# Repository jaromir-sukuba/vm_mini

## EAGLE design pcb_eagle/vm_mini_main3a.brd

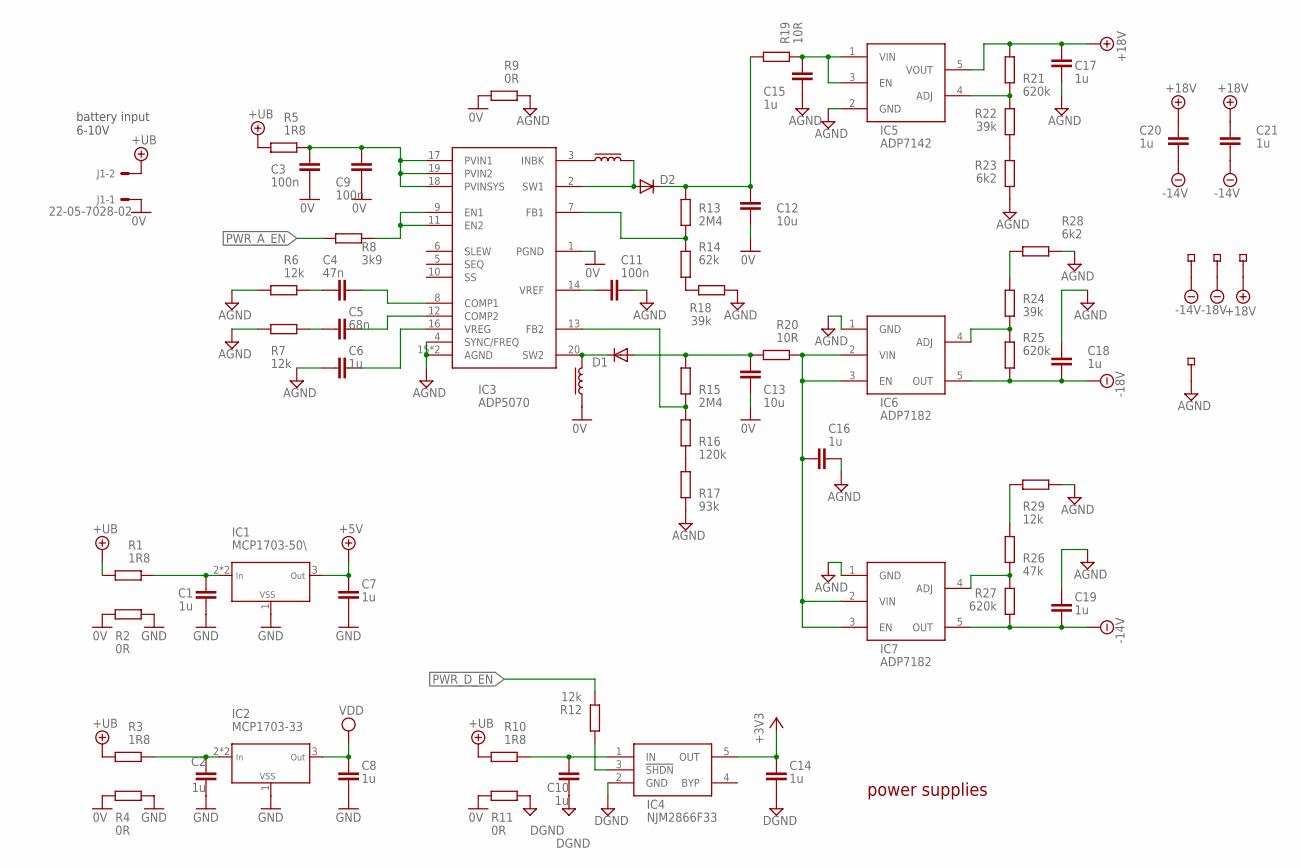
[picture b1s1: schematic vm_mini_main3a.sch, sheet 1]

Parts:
C1, C2, C6, C7, C8, C10, C14, C15, C16, C17, C18, C19, C20, C21: 1u; R0805
C3, C9, C11: 100n; R0805
C4: 47n; R0805
C5: 68n; R0805
C12, C13: 10u; R0805
D1, D2: DIODE-MINIMELF; MINIMELF
IC1: MCP1703-50\; SOT89
IC2: MCP1703-33; SOT89
IC3: ADP5070; TSSOP20-EP
IC4: NJM2866F33; SOT23-5
IC5: ADP7142; SOT23-5L
IC6, IC7: ADP7182; SOT23-5L
J1: 22-05-7028-02; 7395-02
L1, L2: INDUCTORBOURNS_SRP7030; BOURNS_SRP7030
R1, R3, R5, R10: 1R8; R_MINIMELF
R2, R4, R9, R11: 0R; R_MINIMELF
R6, R7, R12, R29: 12k; R_MINIMELF
R8: 3k9; R_MINIMELF
R13, R15: 2M4; R_MINIMELF
R14: 62k; R_MINIMELF
R16: 120k; R_MINIMELF
R17: 93k; R_MINIMELF
R18, R22, R24: 39k; R_MINIMELF
R19, R20: 10R; R_MINIMELF
R21, R25, R27: 620k; R_MINIMELF
R23, R28: 6k2; R_MINIMELF
R26: 47k; R_MINIMELF
TP1, TP2, TP3, TP4: TEST_PADSMD_35X2; TP_SMD_35X2

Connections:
0V: C3.2, C9.2, C12.2, C13.1, IC3.1 (PGND), J1.1, L1.P$1, R2.P$2 (2), R4.P$2 (2), R9.P$2 (2), R11.P$2 (2)
+3V3: C14.2, IC4.5 (OUT); also elsewhere on the board
+5V: C7.2, IC1.3 (OUT); also elsewhere on the board
+18V: C17.1, C20.1, C21.1, IC5.5 (VOUT), R21.P$2 (2), TP3.P$1; also elsewhere on the board
+UB: J1.2, R1.P$2 (2), R3.P$2 (2), R5.P$2 (2), R10.P$2 (2); also elsewhere on the board
-14V: C19.2, C20.2, C21.2, IC7.5 (OUT), R27.P$2 (2), TP1.P$1; also elsewhere on the board
-18V: C18.2, IC6.5 (OUT), R25.P$2 (2), TP2.P$1; also elsewhere on the board
AGND: C6.1, C11.1, C15.2, C16.2, C17.2, C18.1, C19.1, IC3.4 (SYNC/FREQ), IC3.15 (AGND), IC3.EP (AGND), IC5.2 (GND), IC6.1 (GND), IC7.1 (GND), R6.P$2 (2), R7.P$2 (2), R9.P$1 (1), R17.P$1 (1), R18.P$2 (2), R23.P$2 (2), R28.P$2 (2), R29.P$2 (2), TP4.P$1; also elsewhere on the board
DGND: C10.1, C14.1, IC4.2 (GND), R11.P$1 (1); also elsewhere on the board
GND: C1.1, C2.1, C7.1, C8.1, IC1.1 (VSS), IC2.1 (VSS), R2.P$1 (1), R4.P$1 (1); also elsewhere on the board
unnamed: IC3.9 (EN1), IC3.11 (EN2), R8.P$1 (1)
unnamed: IC4.3 (!SHDN), R12.P$2 (2)
unnamed: R24.P$2 (2), R28.P$1 (1)
unnamed: C16.1, IC6.2 (VIN), IC6.3 (EN), IC7.2 (VIN), IC7.3 (EN), R20.P$1 (1)
unnamed: C15.1, IC5.1 (VIN), IC5.3 (EN), R19.P$1 (1)
unnamed: IC3.3 (INBK), L2.P$1
unnamed: D1.C, IC3.20 (SW2), L1.P$2
unnamed: D2.A, IC3.2 (SW1), L2.P$2
unnamed: C3.1, C9.1, IC3.17 (PVIN1), IC3.18 (PVINSYS), IC3.19 (PVIN2), R5.P$1 (1)
unnamed: IC5.4 (ADJ), R21.P$1 (1), R22.P$1 (1)
unnamed: C11.2, IC3.14 (VREF)
unnamed: C12.1, D2.C, R13.P$1 (1), R19.P$2 (2)
unnamed: C4.1, R6.P$1 (1)
unnamed: IC3.13 (FB2), R15.P$1 (1), R16.P$2 (2)
unnamed: C5.1, R7.P$1 (1)
unnamed: IC3.7 (FB1), R13.P$2 (2), R14.P$1 (1)
unnamed: IC6.4 (ADJ), R24.P$1 (1), R25.P$1 (1)
unnamed: C4.2, IC3.8 (COMP1)
unnamed: C5.2, IC3.12 (COMP2)
unnamed: C6.2, IC3.16 (VREG)
unnamed: C13.2, D1.A, R15.P$2 (2), R20.P$2 (2)
unnamed: C10.2, IC4.1 (IN), R10.P$1 (1)
unnamed: C2.2, IC2.2 (IN), IC2.2@1 (IN), R3.P$1 (1)
unnamed: C1.2, IC1.2 (IN), IC1.2@1 (IN), R1.P$1 (1)
unnamed: IC7.4 (ADJ), R26.P$1 (1), R27.P$1 (1)
unnamed: R22.P$2 (2), R23.P$1 (1)
unnamed: R26.P$2 (2), R29.P$1 (1)
unnamed: R16.P$1 (1), R17.P$2 (2)
unnamed: R14.P$2 (2), R18.P$1 (1)
PWR_A_EN: R8.P$2 (2); also elsewhere on the board
PWR_D_EN: R12.P$1 (1); also elsewhere on the board
VDD: C8.2, IC2.3 (OUT); also elsewhere on the board

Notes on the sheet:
power supplies
battery input 6-10V

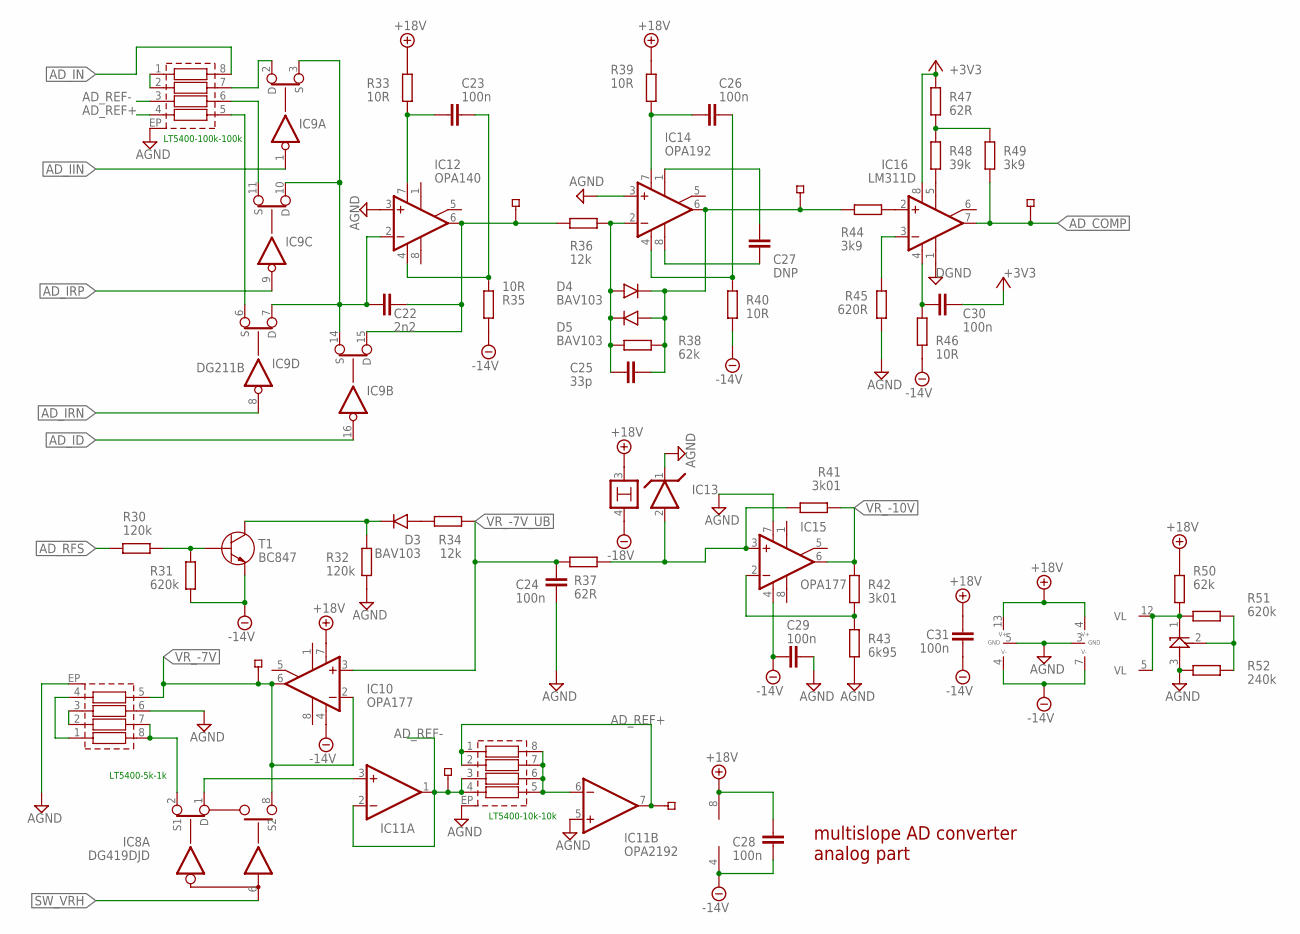
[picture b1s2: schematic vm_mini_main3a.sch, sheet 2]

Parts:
C22: 2n2; C150-054X183
C23, C26, C28, C29, C30, C31: 100n; R0805
C24: 100n; C050-035X075
C25: 33p; R_MINIMELF
C27: DNP; R_MINIMELF
D3, D4, D5: BAV103; SOD-80
IC8: DG419DJD; SO08
IC9: DG211B; SO16
IC10, IC15: OPA177; SO08
IC11: OPA2192; SO08
IC12: OPA140; SO08
IC13: LM399H; TO39/4
IC14: OPA192; SO08
IC16: LM311D; SO08
IC17: TL431_SOT23; SOT23
R30, R32: 120k; R_MINIMELF
R31, R51: 620k; R_MINIMELF
R33, R35, R39, R40, R46: 10R; R_MINIMELF
R34, R36: 12k; R_MINIMELF
R37, R47: 62R; R_MINIMELF
R38, R50: 62k; R_MINIMELF
R41, R42: 3k01; R_TR191
R43: 6k95; R_TR191
R44, R49: 3k9; R_MINIMELF
R45: 620R; R_MINIMELF
R48: 39k; R_MINIMELF
R52: 240k; R_MINIMELF
RN1: LT5400-5k-1k; MSOP8-EP
RN2: LT5400-100k-100k; MSOP8-EP
RN3: LT5400-10k+10k; MSOP8-EP
T1: BC847; SOT23
TP5, TP6, TP7, TP8, TP9, TP21: TEST_PADSMD_35X2; TP_SMD_35X2

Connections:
+3V3: C30.1, IC16.8 (V+), R47.P$2 (2); also elsewhere on the board
+18V: C28.2, C31.2, IC8.4 (V+), IC9.13 (V+), IC10.7 (V+), IC11.8 (V+), IC13.3, R33.P$2 (2), R39.P$2 (2), R50.P$1 (1); also elsewhere on the board
-14V: C28.1, C29.1, C31.1, IC8.7 (V-), IC9.4 (V-), IC10.4 (V-), IC11.4 (V-), IC15.4 (V-), R31.P$1 (1), R35.P$2 (2), R40.P$2 (2), R46.P$2 (2), T1.2 (E); also elsewhere on the board
-18V: IC13.4; also elsewhere on the board
AD_COMP: IC16.7 (OUT), R49.P$1 (1), TP7.P$1; also elsewhere on the board
AD_ID: IC9.16 (IN); also elsewhere on the board
AD_IIN: IC9.1 (IN); also elsewhere on the board
AD_IN: RN2.8 (R1B); also elsewhere on the board
AD_IRN: IC9.8 (IN); also elsewhere on the board
AD_IRP: IC9.9 (IN); also elsewhere on the board
AD_REF+: IC11.7 (OUT), RN2.4 (R4A), RN3.1 (R1A), RN3.2 (R2A), TP8.P$1
AD_REF-: IC11.1 (OUT), IC11.2 (-IN), RN2.3 (R3A), RN3.3 (R3A), RN3.4 (R4A), TP9.P$1
AD_RFS: R30.P$2 (2); also elsewhere on the board
AGND: C24.2, C29.2, IC8.3 (GND), IC9.5 (GND), IC11.5 (+IN), IC12.3 (+IN), IC13.1, IC14.3 (+IN), IC15.7 (V+), IC17.3 (A), R32.P$2 (2), R43.P$1 (1), R45.P$2 (2), R52.P$1 (1), RN1.6 (R3B), RN1.EP (SH), RN2.EP (SH), RN3.EP (SH); also elsewhere on the board
DGND: IC16.1 (GND); also elsewhere on the board
unnamed: C22.1, IC9.3 (S), IC9.7 (D), IC9.10 (D), IC9.14 (S), IC12.2 (-IN)
unnamed: IC15.2 (-IN), R42.P$2 (2), R43.P$2 (2)
unnamed: IC9.2 (D), RN2.7 (R2B)
unnamed: C22.2, IC9.15 (D), IC12.6 (OUT), R36.P$1 (1), TP5.P$1
unnamed: IC9.11 (S), RN2.6 (R3B)
unnamed: IC9.6 (S), RN2.5 (R4B)
unnamed: C23.2, IC12.7 (V+), R33.P$1 (1)
unnamed: C23.1, IC12.4 (V-), R35.P$1 (1)
unnamed: IC8.1 (D), IC11.3 (+IN)
unnamed: RN1.1 (R1A), RN1.4 (R4A)
unnamed: D3.A, R34.P$2 (2)
unnamed: IC8.2 (S1), RN1.7 (R2B), RN1.8 (R1B)
unnamed: IC13.2, IC15.3 (+IN), R37.P$1 (1), R41.P$2 (2)
unnamed: C25.P$1 (1), D4.A, D5.K, IC14.2 (-IN), R36.P$2 (2), R38.P$1 (1)
unnamed: R30.P$1 (1), R31.P$2 (2), T1.1 (B)
unnamed: D3.K, R32.P$1 (1), T1.3 (C)
unnamed: RN2.1 (R1A), RN2.2 (R2A)
unnamed: IC11.6 (-IN), RN3.5 (R4B), RN3.6 (R3B), RN3.7 (R2B), RN3.8 (R1B)
unnamed: RN1.2 (R2A), RN1.3 (R3A)
unnamed: C26.2, IC14.7 (V+), R39.P$1 (1)
unnamed: C26.1, IC14.4 (V-), R40.P$1 (1)
unnamed: C25.P$2 (2), D4.K, D5.A, IC14.6 (OUT), R38.P$2 (2), R44.P$1 (1), TP6.P$1
unnamed: IC16.5 (ON), R48.P$1 (1)
unnamed: R47.P$1 (1), R48.P$2 (2), R49.P$2 (2)
unnamed: C30.2, IC16.4 (V-), R46.P$1 (1)
unnamed: IC16.2 (+IN), R44.P$2 (2)
unnamed: IC16.3 (-IN), R45.P$1 (1)
unnamed: IC17.2 (R), R51.P$2 (2), R52.P$2 (2)
unnamed: IC8.5 (VL), IC9.12 (VL), IC17.1 (C), R50.P$2 (2), R51.P$1 (1)
unnamed: C27.P$1 (1), IC14.8 (OPT)
unnamed: C27.P$2 (2), IC14.1 (ON1)
SW_VRH: IC8.6 (IN)
VR_-7V: IC8.8 (S2), IC10.2 (-IN), IC10.6 (OUT), RN1.5 (R4B), TP21.P$1; also elsewhere on the board
VR_-7V_UB: C24.1, IC10.3 (+IN), R34.P$1 (1), R37.P$2 (2)
VR_-10V: IC15.6 (OUT), R41.P$1 (1), R42.P$1 (1)

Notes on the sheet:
LT5400-5k-1k
LT5400-10k-10k
LT5400-100k-100k
multislope AD converter analog part

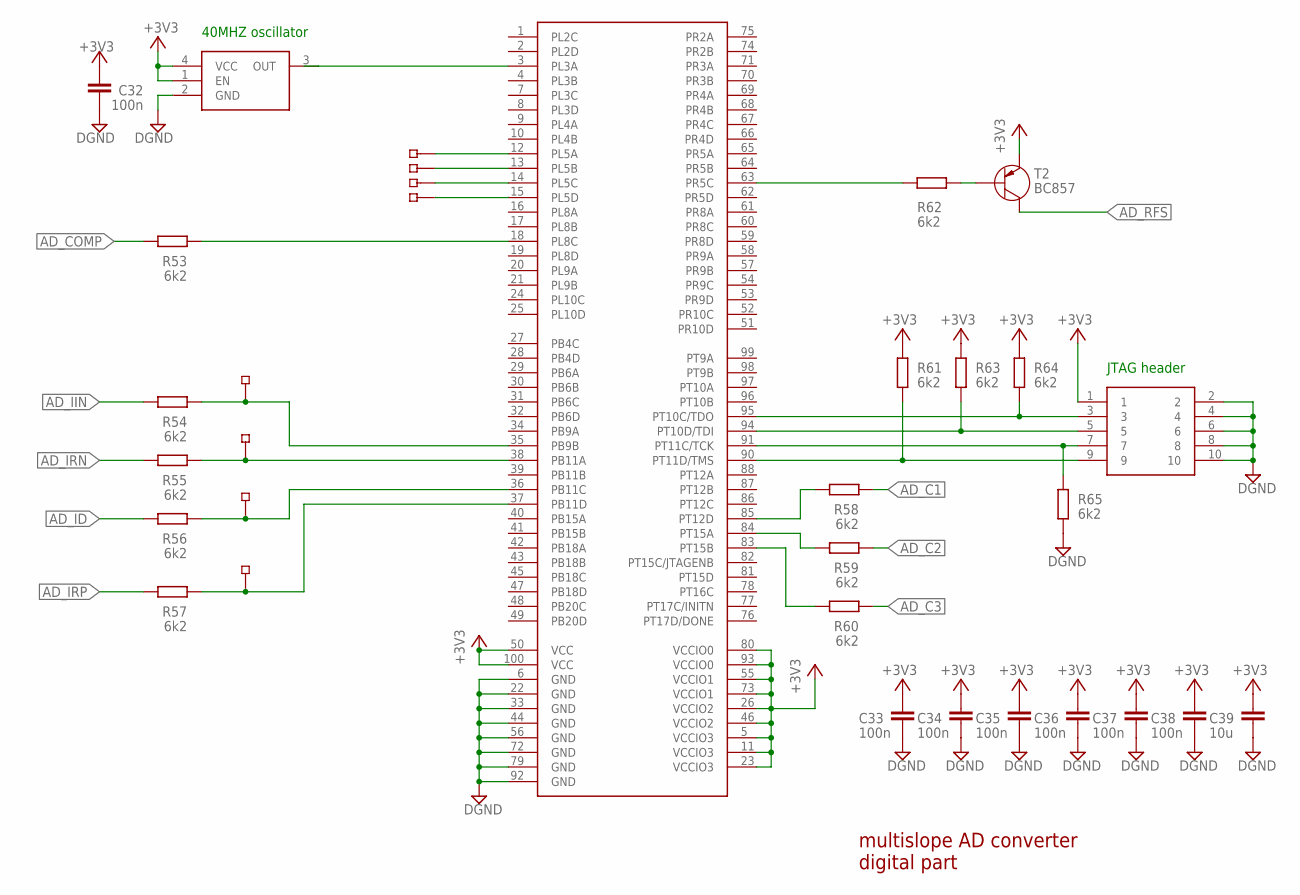
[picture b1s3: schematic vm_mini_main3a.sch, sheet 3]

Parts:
C32, C33, C34, C35, C36, C37, C38: 100n; R0805
C39: 10u; R0805
CON1: IDC_10_2MM; IDC_20_10P
IC18: MACHXO2-1200-TQ100T100; TQFP100
OSC1: OSC3225; OSC_3225
R53, R54, R55, R56, R57, R58, R59, R60, R61, R62, R63, R64, R65: 6k2; R_MINIMELF
T2: BC857; SOT23
TP10, TP11, TP12, TP13, TP14, TP15, TP16, TP17: TEST_PADSMD_35X2; TP_SMD_35X2

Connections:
+3V3: C32.2, C33.2, C34.2, C35.2, C36.2, C37.2, C38.2, C39.2, CON1.1, IC18.5 (VCCIO3), IC18.11 (VCCIO3), IC18.23 (VCCIO3), IC18.26 (VCCIO2), IC18.46 (VCCIO2), IC18.50 (VCC), IC18.55 (VCCIO1), IC18.73 (VCCIO1), IC18.80 (VCCIO0), IC18.93 (VCCIO0), IC18.100 (VCC), OSC1.1 (EN), OSC1.4 (VCC), R61.P$1 (1), R63.P$1 (1), R64.P$1 (1), T2.2 (C); also elsewhere on the board
AD_C1: R58.P$2 (2); also elsewhere on the board
AD_C2: R59.P$2 (2); also elsewhere on the board
AD_C3: R60.P$2 (2); also elsewhere on the board
AD_COMP: R53.P$1 (1); also elsewhere on the board
AD_ID: R56.P$1 (1); also elsewhere on the board
AD_IIN: R54.P$1 (1); also elsewhere on the board
AD_IRN: R55.P$1 (1); also elsewhere on the board
AD_IRP: R57.P$1 (1); also elsewhere on the board
AD_RFS: T2.3 (E); also elsewhere on the board
DGND: C32.1, C33.1, C34.1, C35.1, C36.1, C37.1, C38.1, C39.1, CON1.2, CON1.4, CON1.6, CON1.8, CON1.10, IC18.6 (GND), IC18.22 (GND), IC18.33 (GND), IC18.44 (GND), IC18.56 (GND), IC18.72 (GND), IC18.79 (GND), IC18.92 (GND), OSC1.2 (GND), R65.P$2 (2); also elsewhere on the board
unnamed: IC18.3 (PL3A), OSC1.3 (OUT)
unnamed: R62.P$1 (1), T2.1 (B)
unnamed: IC18.35 (PB9B), R54.P$2 (2), TP10.P$1
unnamed: CON1.9, IC18.90 (PT11D/TMS), R61.P$2 (2)
unnamed: CON1.7, IC18.91 (PT11C/TCK), R65.P$1 (1)
unnamed: CON1.5, IC18.94 (PT10D/TDI), R63.P$2 (2)
unnamed: CON1.3, IC18.95 (PT10C/TDO), R64.P$2 (2)
unnamed: IC18.84 (PT15A), R59.P$1 (1)
unnamed: IC18.36 (PB11C), R56.P$2 (2), TP13.P$1
unnamed: IC18.83 (PT15B), R60.P$1 (1)
unnamed: IC18.37 (PB11D), R57.P$2 (2), TP11.P$1
unnamed: IC18.38 (PB11A), R55.P$2 (2), TP12.P$1
unnamed: IC18.18 (PL8C), R53.P$2 (2)
unnamed: IC18.63 (PR5C), R62.P$2 (2)
unnamed: IC18.85 (PT12D), R58.P$1 (1)
unnamed: IC18.12 (PL5A), TP14.P$1
unnamed: IC18.13 (PL5B), TP15.P$1
unnamed: IC18.14 (PL5C), TP16.P$1
unnamed: IC18.15 (PL5D), TP17.P$1

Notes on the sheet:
multislope AD converter digital part
JTAG header
40MHZ oscillator

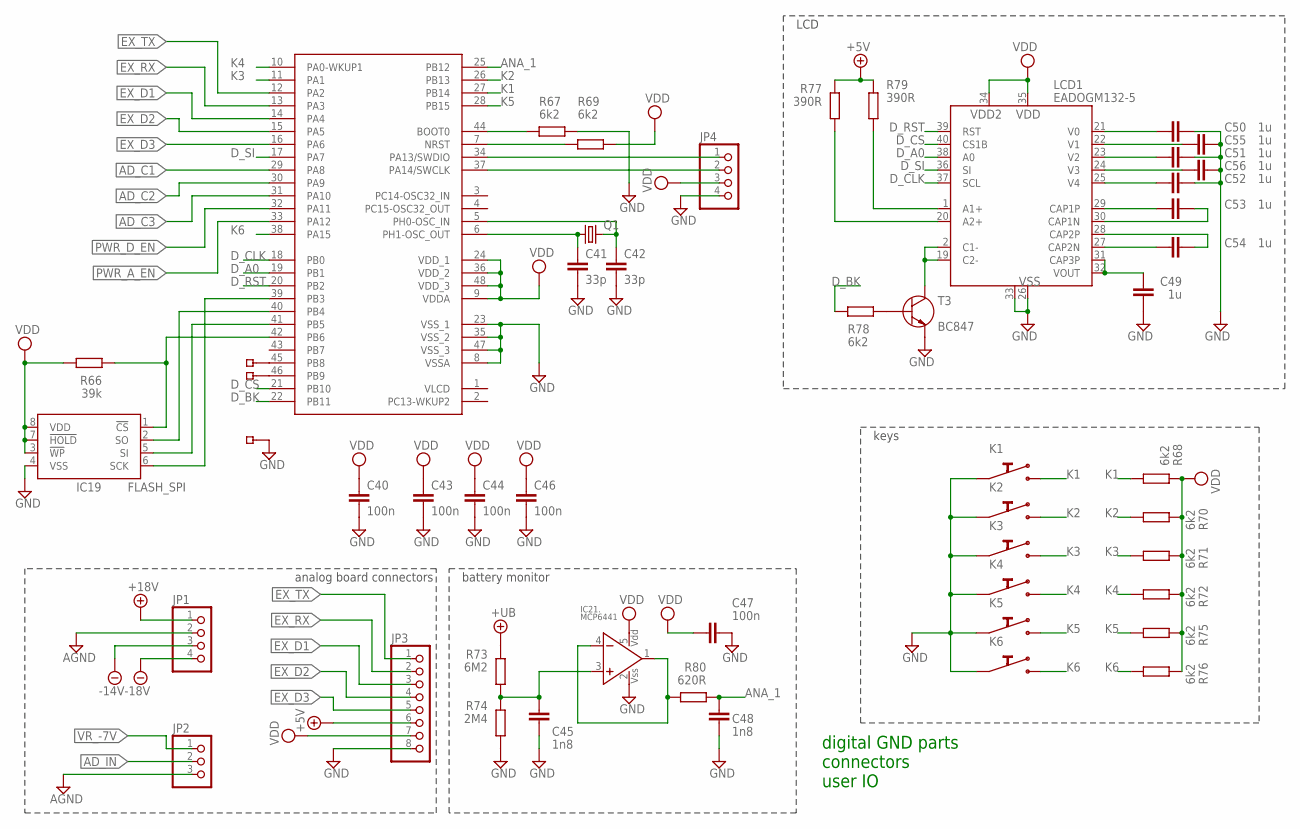
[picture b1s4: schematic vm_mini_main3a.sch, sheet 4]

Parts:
C40, C43, C44, C46, C47: 100n; R0805
C41, C42: 33p; R0805
C45, C48: 1n8; R_MINIMELF
C49, C50, C51, C52, C53, C54, C55, C56: 1u; R0805
IC19: FLASH_SPI; SO-08
IC20: STM32L152XC_LQFP48; LQFP48
IC21: MCP6441; SOT23-5L
JP1: PINHD-1X04_2.54; 1X04
JP2: PINHD-1X03_2.54; 1X03
JP3: PINHD-1X08_2.54; 1X08
JP4: PINHD-1X04_2.54-90°; 1X04/90
K1, K2, K3, K4, K5, K6: SWITCH_MINI6450; SWITCH_6450
LCD1: EADOGM132-5; EADOGM
Q1: CRYSTALHC49UP; HC49UP
R66: 39k; R_MINIMELF
R67, R68, R69, R70, R71, R72, R75, R76, R78: 6k2; R_MINIMELF
R73: 6M2; R_MINIMELF
R74: 2M4; R_MINIMELF
R77, R79: 390R; R_MINIMELF
R80: 620R; R_MINIMELF
T3: BC847; SOT23
TP18, TP19, TP20: TEST_PADSMD_35X2; TP_SMD_35X2

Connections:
+5V: JP3.6, R77.P$2 (2), R79.P$2 (2); also elsewhere on the board
+18V: JP1.1; also elsewhere on the board
+UB: R73.P$1 (1); also elsewhere on the board
-14V: JP1.3; also elsewhere on the board
-18V: JP1.4; also elsewhere on the board
AD_C1: IC20.29 (PA8); also elsewhere on the board
AD_C2: IC20.30 (PA9); also elsewhere on the board
AD_C3: IC20.31 (PA10); also elsewhere on the board
AD_IN: JP2.2; also elsewhere on the board
AGND: JP1.2, JP2.3; also elsewhere on the board
ANA_1: C48.P$1 (1), IC20.25 (PB12), R80.P$2 (2)
D_A0: IC20.19 (PB1), LCD1.38 (A0)
D_BK: IC20.22 (PB11), R78.P$2 (2)
D_CLK: IC20.18 (PB0), LCD1.37 (SCL)
D_CS: IC20.21 (PB10), LCD1.40 (CS1B)
D_RST: IC20.20 (PB2), LCD1.39 (RST)
D_SI: IC20.17 (PA7), LCD1.36 (SI)
EX_D1: IC20.14 (PA4), JP3.3
EX_D2: IC20.15 (PA5), JP3.4
EX_D3: IC20.16 (PA6), JP3.5
EX_RX: IC20.13 (PA3), JP3.2
EX_TX: IC20.12 (PA2), JP3.1
GND: C40.2, C41.2, C42.2, C43.2, C44.2, C45.P$2 (2), C46.2, C47.2, C48.P$2 (2), C49.2, C50.2, C51.2, C52.2, C55.2, C56.2, IC19.4 (VSS), IC20.8 (VSSA), IC20.23 (VSS_1), IC20.35 (VSS_2), IC20.47 (VSS_3), IC21.2 (VSS), JP3.8, JP4.4, K1.P$1, K2.P$1, K3.P$1, K4.P$1, K5.P$1, K6.P$1, LCD1.26 (VSS), LCD1.33 (VSS1), R67.P$2 (2), R74.P$2 (2), T3.2 (E), TP20.P$1; also elsewhere on the board
K1: IC20.27 (PB14), K1.P$2, R68.P$1 (1)
K2: IC20.26 (PB13), K2.P$2, R70.P$1 (1)
K3: IC20.11 (PA1), K3.P$2, R71.P$1 (1)
K4: IC20.10 (PA0-WKUP1), K4.P$2, R72.P$1 (1)
K5: IC20.28 (PB15), K5.P$2, R75.P$1 (1)
K6: IC20.38 (PA15), K6.P$2, R76.P$1 (1)
unnamed: LCD1.1 (A1+), R79.P$1 (1)
unnamed: LCD1.20 (A2+), R77.P$1 (1)
unnamed: LCD1.2 (C1-), LCD1.19 (C2-), T3.3 (C)
unnamed: R78.P$1 (1), T3.1 (B)
unnamed: C50.1, LCD1.21 (V0)
unnamed: C55.1, LCD1.22 (V1)
unnamed: C51.1, LCD1.23 (V2)
unnamed: C56.1, LCD1.24 (V3)
unnamed: C52.1, LCD1.25 (V4)
unnamed: C53.1, LCD1.29 (CAP1P)
unnamed: C53.2, LCD1.30 (CAP1N)
unnamed: C54.2, LCD1.28 (CAP2P)
unnamed: C54.1, LCD1.27 (CAP2N)
unnamed: C49.1, LCD1.31 (CAP3P), LCD1.32 (VOUT)
unnamed: IC20.34 (PA13/SWDIO), JP4.1
unnamed: IC20.37 (PA14/SWCLK), JP4.2
unnamed: C41.1, IC20.6 (PH1-OSC_OUT), Q1.1
unnamed: C42.1, IC20.5 (PH0-OSC_IN), Q1.2
unnamed: IC20.44 (BOOT0), R67.P$1 (1)
unnamed: IC20.7 (NRST), R69.P$1 (1)
unnamed: C45.P$1 (1), IC21.3 (NEIN+), R73.P$2 (2), R74.P$1 (1)
unnamed: IC19.6 (SCK), IC20.39 (PB3)
unnamed: IC21.1 (VYSTUP), IC21.4 (IN-), R80.P$1 (1)
unnamed: IC19.2 (SO), IC20.40 (PB4)
unnamed: IC19.5 (SI), IC20.41 (PB5)
unnamed: IC19.1 (!CS), IC20.42 (PB6), R66.P$2 (2)
unnamed: IC20.45 (PB8), TP18.P$1
unnamed: IC20.46 (PB9), TP19.P$1
PWR_A_EN: IC20.33 (PA12); also elsewhere on the board
PWR_D_EN: IC20.32 (PA11); also elsewhere on the board
VDD: C40.1, C43.1, C44.1, C46.1, C47.1, IC19.3 (!WP), IC19.7 (!HOLD), IC19.8 (VDD), IC20.9 (VDDA), IC20.24 (VDD_1), IC20.36 (VDD_2), IC20.48 (VDD_3), IC21.5 (VDD), JP3.7, JP4.3, LCD1.34 (VDD2), LCD1.35 (VDD), R66.P$1 (1), R68.P$2 (2), R69.P$2 (2), R70.P$2 (2), R71.P$2 (2), R72.P$2 (2), R75.P$2 (2), R76.P$2 (2); also elsewhere on the board
VR_-7V: JP2.1; also elsewhere on the board

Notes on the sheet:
digital GND parts connectors user IO
battery monitor
analog board connectors
keys
LCD

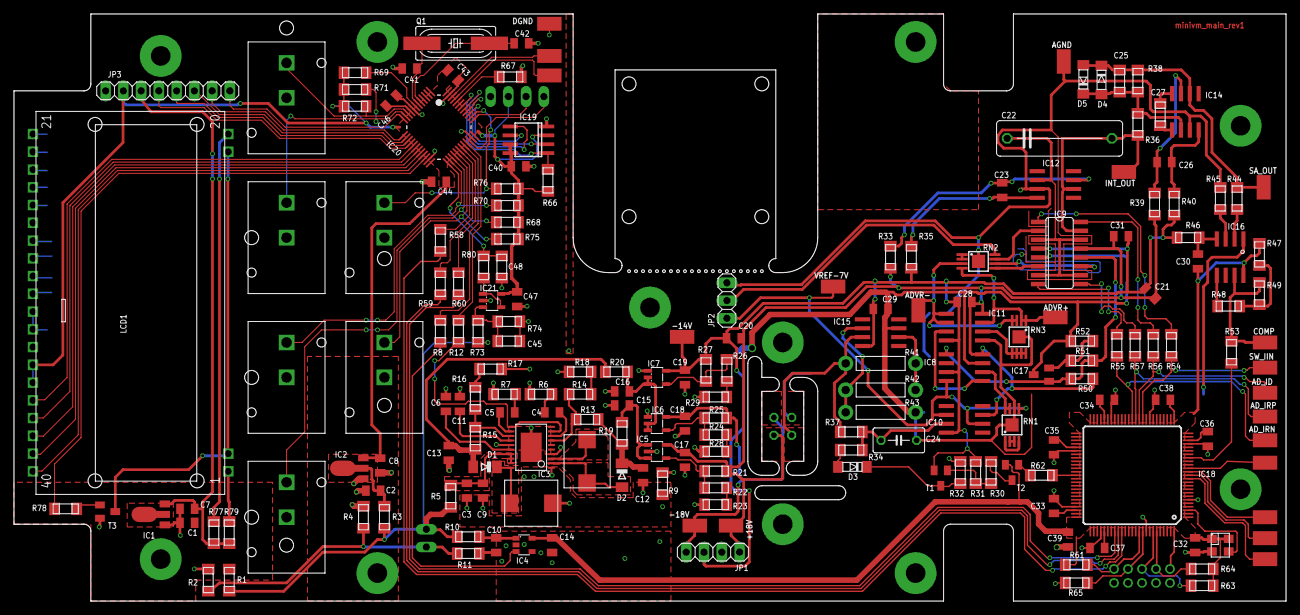
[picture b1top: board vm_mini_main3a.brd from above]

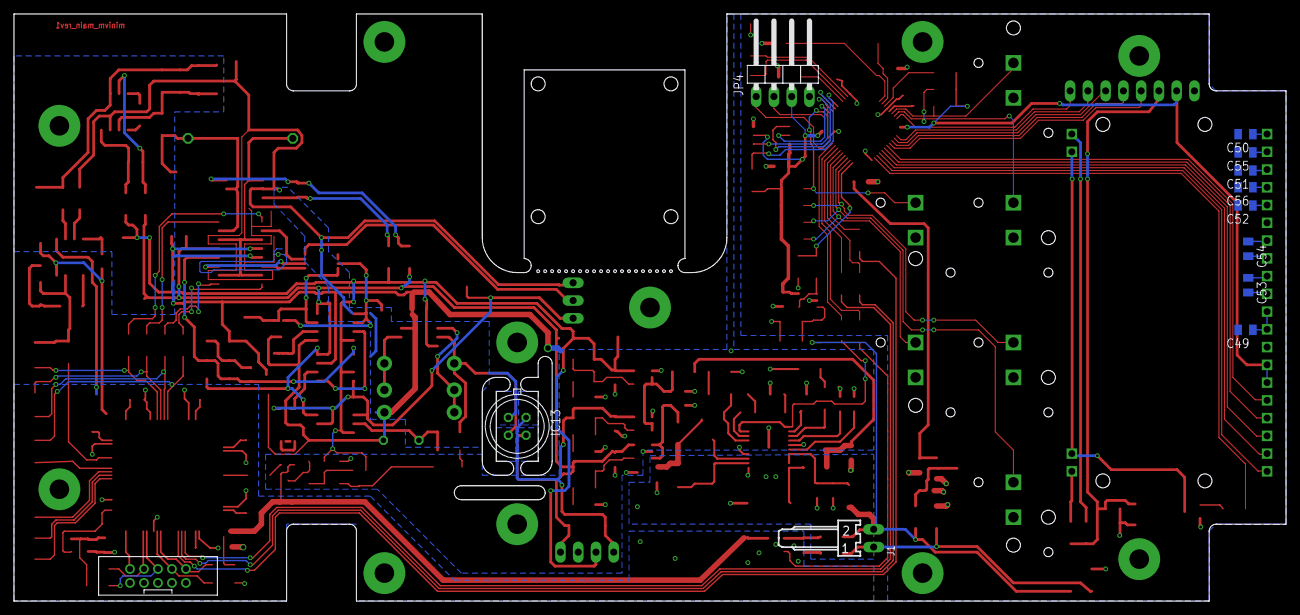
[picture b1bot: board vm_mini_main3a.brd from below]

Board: 2 copper layers, 182.0 x 84.0 mm, 206 parts (12 on the bottom side), 153 nets.

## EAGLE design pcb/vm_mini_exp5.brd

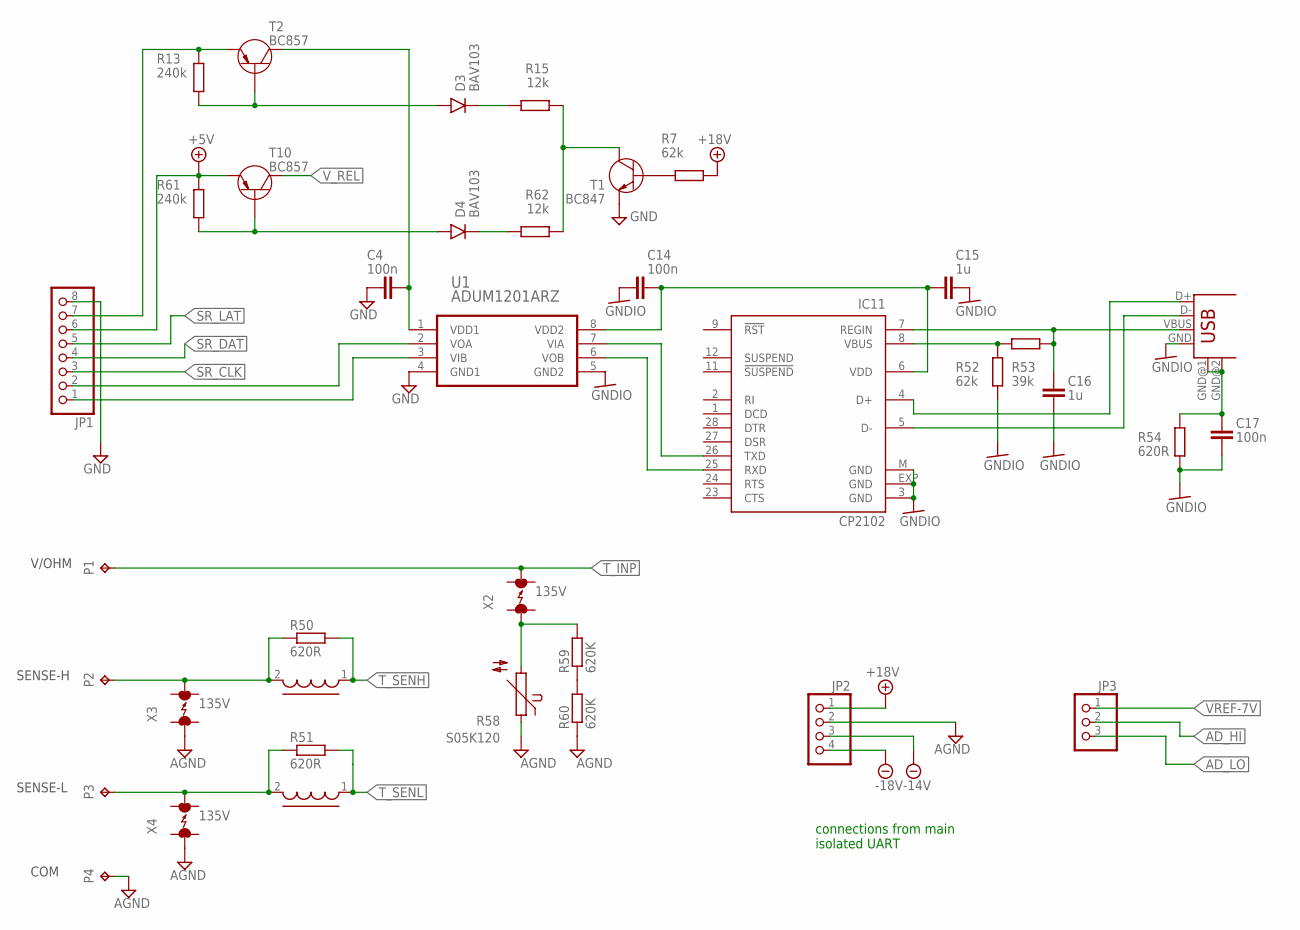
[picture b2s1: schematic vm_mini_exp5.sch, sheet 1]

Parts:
C4, C14, C17: 100n; R0805
C15, C16: 1u; R0805
D3, D4: BAV103; SOD-80
IC11: CP2102; MLP28
JP1: PINHD-1X08_2.54; 1X08
JP2: PINHD-1X04_2.54; 1X04
JP3: PINHD-1X03_2.54; 1X03
P1, P2, P3, P4: TPPAD1-17; P1-17
R7, R52: 62k; R_MINIMELF
R13, R61: 240k; R_MINIMELF
R15, R62: 12k; R_MINIMELF
R50, R51, R54: 620R; R_MINIMELF
R53: 39k; R_MINIMELF
R58: S05K120; S05K175
R59, R60: 620K; R_MINIMELF
T1: BC847; SOT23
T2, T10: BC857; SOT23
U1: ADUM1201ARZ; SOIC127P600X175-8N
U$7, U$8: INDUCTOR_GEN1210; 1210
USB1: USB-B-H
X2, X3, X4: 135V; EPCOS_N81

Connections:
+5V: JP1.6, R61.P$1 (1), T10.2 (C); also elsewhere on the board
+18V: JP2.1, R7.P$2 (2); also elsewhere on the board
-14V: JP2.3; also elsewhere on the board
-18V: JP2.4; also elsewhere on the board
AD_HI: JP3.2; also elsewhere on the board
AD_LO: JP3.3; also elsewhere on the board
AGND: JP2.2, P4.TP, R58.1, R60.P$1 (1), X3.1, X4.1; also elsewhere on the board
GND: C4.1, JP1.8, T1.2 (E), U1.4 (GND1); also elsewhere on the board
GNDIO: C14.1, C15.2, C16.1, C17.1, IC11.3 (GND), IC11.EXP (GND), IC11.M (GND), R52.P$2 (2), R54.P$2 (2), U1.5 (GND2), USB1.GND
unnamed: JP1.1, U1.3 (VIB)
unnamed: JP1.2, U1.2 (VOA)
unnamed: IC11.4 (D+), USB1.D+
unnamed: IC11.5 (D-), USB1.D-
unnamed: C16.2, IC11.7 (REGIN), R53.P$1 (1), USB1.VBUS
unnamed: R58.2, R59.P$2 (2), X2.1
unnamed: IC11.26 (TXD), U1.7 (VIA)
unnamed: IC11.25 (RXD), U1.6 (VOB)
unnamed: C14.2, C15.1, IC11.6 (VDD), U1.8 (VDD2)
unnamed: IC11.8 (VBUS), R52.P$1 (1), R53.P$2 (2)
unnamed: C17.2, R54.P$1 (1), USB1.GND@1 (GND), USB1.GND@2 (GND)
unnamed: R15.P$1 (1), R62.P$1 (1), T1.3 (C)
unnamed: D3.A, R13.P$2 (2), T2.1 (B)
unnamed: D4.K, R62.P$2 (2)
unnamed: R7.P$1 (1), T1.1 (B)
unnamed: R59.P$1 (1), R60.P$2 (2)
unnamed: P3.TP, R51.P$1 (1), U$8.2, X4.2
unnamed: P2.TP, R50.P$1 (1), U$7.2, X3.2
unnamed: JP1.7, R13.P$1 (1), T2.2 (C)
unnamed: D4.A, R61.P$2 (2), T10.1 (B)
unnamed: C4.2, T2.3 (E), U1.1 (VDD1)
unnamed: D3.K, R15.P$2 (2)
SR_CLK: JP1.3; also elsewhere on the board
SR_DAT: JP1.4; also elsewhere on the board
SR_LAT: JP1.5; also elsewhere on the board
T_INP: P1.TP, X2.2; also elsewhere on the board
T_SENH: R50.P$2 (2), U$7.1; also elsewhere on the board
T_SENL: R51.P$2 (2), U$8.1; also elsewhere on the board
VREF-7V: JP3.1; also elsewhere on the board
V_REL: T10.3 (E); also elsewhere on the board

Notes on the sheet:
V/OHM
SENSE-H
SENSE-L
COM
connections from main isolated UART

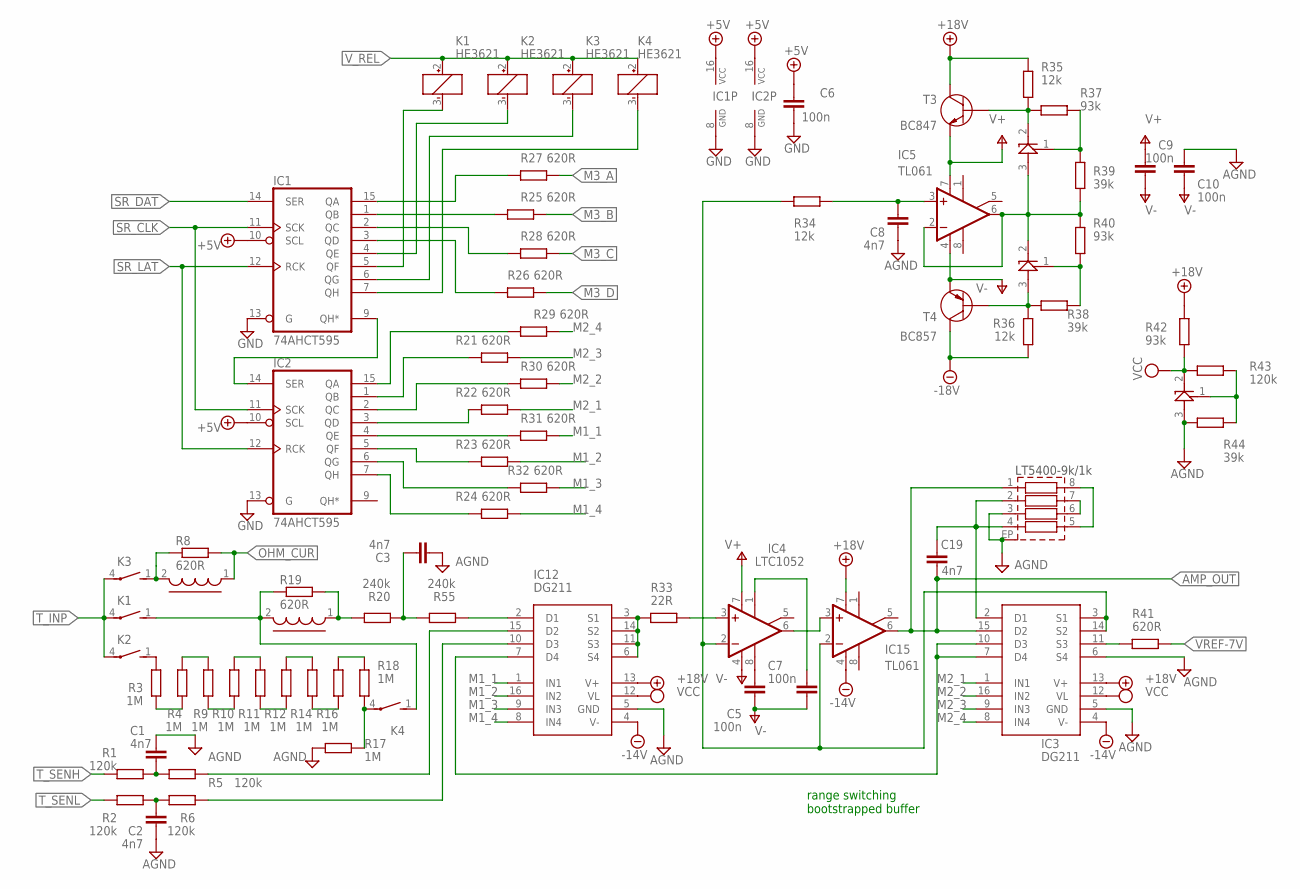
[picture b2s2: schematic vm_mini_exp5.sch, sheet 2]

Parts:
C1, C2, C3, C8, C19: 4n7; C050-025X075
C5, C7: 100n; C050-045X075
C6, C9, C10: 100n; R0805
IC1, IC2: 74AHCT595; SO16
IC3, IC12: DG211; SO-16
IC4: LTC1052; DIL08
IC5, IC15: TL061; SO08
IC6, IC13, IC14: TL431_SOT23; SOT23
K1, K2, K3, K4: HE3621
R1, R2, R5, R6, R43: 120k; R_MINIMELF
R3, R4, R9, R10, R11, R12, R14, R16, R17, R18: 1M; R_MINIMELF
R8, R19, R21, R22, R23, R24, R25, R26, R27, R28, R29, R30, R31, R32, R41: 620R; R_MINIMELF
R20, R55: 240k; R_MINIMELF
R33: 22R; R_MINIMELF
R34, R35, R36: 12k; R_MINIMELF
R37, R40, R42: 93k; R_MINIMELF
R38, R39, R44: 39k; R_MINIMELF
RN3: LT5400; MSOP8-EP
T3: BC847; SOT23
T4: BC857; SOT23
U$1, U$2: INDUCTOR_GEN1210; 1210

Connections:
+5V: C6.1, IC1.10 (SCL), IC1.16 (VCC), IC2.10 (SCL), IC2.16 (VCC); also elsewhere on the board
+18V: IC3.13 (V+), IC12.13 (V+), IC15.7 (V+), R35.P$2 (2), R42.P$2 (2), T3.3 (C); also elsewhere on the board
-14V: IC3.4 (V-), IC12.4 (V-), IC15.4 (V-); also elsewhere on the board
-18V: R36.P$1 (1), T4.3 (E); also elsewhere on the board
AGND: C1.1, C2.1, C3.1, C8.1, C10.1, IC3.5 (GND), IC3.6 (S4), IC6.3 (A), IC12.5 (GND), R17.P$2 (2), R44.P$1 (1), RN3.3 (R3A), RN3.EP (SH); also elsewhere on the board
AGND1: IC14.3 (A), R36.P$2 (2), R38.P$1 (1), T4.1 (B)
AMP_OUT: C19.1, IC3.15 (D2), IC15.6 (OUT), RN3.1 (R1A); also elsewhere on the board
GND: C6.2, IC1.8 (GND), IC1.13 (G), IC2.8 (GND), IC2.13 (G); also elsewhere on the board
M1_1: IC12.1 (IN1), R31.P$1 (1)
M1_2: IC12.16 (IN2), R23.P$1 (1)
M1_3: IC12.9 (IN3), R32.P$1 (1)
M1_4: IC12.8 (IN4), R24.P$1 (1)
M2_1: IC3.1 (IN1), R22.P$1 (1)
M2_2: IC3.16 (IN2), R30.P$1 (1)
M2_3: IC3.9 (IN3), R21.P$1 (1)
M2_4: IC3.8 (IN4), R29.P$1 (1)
M3_A: R27.P$1 (1); also elsewhere on the board
M3_B: R25.P$1 (1); also elsewhere on the board
M3_C: R28.P$1 (1); also elsewhere on the board
M3_D: R26.P$1 (1); also elsewhere on the board
unnamed: IC3.7 (D4), IC3.10 (D3), IC12.7 (D4)
unnamed: RN3.5 (R4B), RN3.8 (R1B)
unnamed: C19.2, IC3.2 (D1), RN3.2 (R2A), RN3.4 (R4A)
unnamed: RN3.6 (R3B), RN3.7 (R2B)
unnamed: R3.P$1 (1), R4.P$1 (1)
unnamed: IC12.3 (S1), IC12.6 (S4), IC12.11 (S3), IC12.14 (S2), R33.P$1 (1)
unnamed: R4.P$2 (2), R9.P$2 (2)
unnamed: R9.P$1 (1), R10.P$1 (1)
unnamed: R10.P$2 (2), R11.P$2 (2)
unnamed: R11.P$1 (1), R12.P$1 (1)
unnamed: R12.P$2 (2), R14.P$2 (2)
unnamed: R14.P$1 (1), R16.P$1 (1)
unnamed: R16.P$2 (2), R18.P$2 (2)
unnamed: K4.4, R17.P$1 (1), R18.P$1 (1)
unnamed: K2.1 (S), R3.P$2 (2)
unnamed: IC1.5 (QF), K1.3 (-)
unnamed: R19.P$2 (2), R20.P$2 (2), U$2.1
unnamed: IC1.4 (QE), K2.3 (-)
unnamed: IC1.6 (QG), K3.3 (-)
unnamed: C3.2, R20.P$1 (1), R55.P$2 (2)
unnamed: IC4.3 (+IN), R33.P$2 (2)
unnamed: IC1.7 (QH), K4.3 (-)
unnamed: C1.2, R1.P$1 (1), R5.P$2 (2)
unnamed: IC5.2 (-IN), IC5.6 (OUT), IC13.3 (A), IC14.2 (C), R39.P$1 (1), R40.P$1 (1)
unnamed: C5.2, IC4.8 (OPT)
unnamed: C7.2, IC4.1 (ON1)
unnamed: C2.2, R2.P$1 (1), R6.P$2 (2)
unnamed: IC12.15 (D2), R5.P$1 (1)
unnamed: C8.2, IC5.3 (+IN), R34.P$2 (2)
unnamed: IC12.10 (D3), R6.P$1 (1)
unnamed: IC1.9 (QH*), IC2.14 (SER)
unnamed: IC1.15 (QA), R27.P$2 (2)
unnamed: IC1.1 (QB), R25.P$2 (2)
unnamed: IC1.2 (QC), R28.P$2 (2)
unnamed: IC1.3 (QD), R26.P$2 (2)
unnamed: IC2.15 (QA), R29.P$2 (2)
unnamed: IC2.1 (QB), R21.P$2 (2)
unnamed: IC3.3 (S1), IC3.14 (S2), IC4.2 (-IN), IC15.2 (-IN), R34.P$1 (1)
unnamed: IC2.2 (QC), R30.P$2 (2)
unnamed: IC2.3 (QD), R22.P$2 (2)
unnamed: IC2.4 (QE), R31.P$2 (2)
unnamed: IC12.2 (D1), R55.P$1 (1)
unnamed: IC3.11 (S3), R41.P$1 (1)
unnamed: IC2.7 (QH), R24.P$2 (2)
unnamed: IC2.6 (QG), R32.P$2 (2)
unnamed: IC2.5 (QF), R23.P$2 (2)
unnamed: IC13.2 (C), R35.P$1 (1), R37.P$1 (1), T3.1 (B)
unnamed: IC13.1 (R), R37.P$2 (2), R39.P$2 (2)
unnamed: IC6.1 (R), R43.P$2 (2), R44.P$2 (2)
unnamed: IC14.1 (R), R38.P$2 (2), R40.P$2 (2)
unnamed: K1.1 (S), K4.1 (S), R19.P$1 (1), U$2.2
unnamed: K3.1 (S), R8.P$1 (1), U$1.2
unnamed: IC4.6 (OUT), IC15.3 (+IN)
OHM_CUR: R8.P$2 (2), U$1.1; also elsewhere on the board
SR_CLK: IC1.11 (SCK), IC2.11 (SCK); also elsewhere on the board
SR_DAT: IC1.14 (SER); also elsewhere on the board
SR_LAT: IC1.12 (RCK), IC2.12 (RCK); also elsewhere on the board
T_INP: K1.4, K2.4, K3.4; also elsewhere on the board
T_SENH: R1.P$2 (2); also elsewhere on the board
T_SENL: R2.P$2 (2); also elsewhere on the board
V+: C9.1, IC4.7 (V+), IC5.7 (V+), T3.2 (E)
V-: C5.1, C7.1, C9.2, C10.2, IC4.4 (V-), IC5.4 (V-), T4.2 (C)
VCC: IC3.12 (VL), IC6.2 (C), IC12.12 (VL), R42.P$1 (1), R43.P$1 (1); also elsewhere on the board
VREF-7V: R41.P$2 (2); also elsewhere on the board
V_REL: K1.2 (+), K2.2 (+), K3.2 (+), K4.2 (+); also elsewhere on the board

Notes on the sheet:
LT5400-9k/1k
range switching bootstrapped buffer
